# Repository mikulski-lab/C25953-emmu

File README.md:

# Atari XE C25953 emmu unit replicated in GAL16v8 and GAL20v10

As the happy owner of an Atari 65XE I wanted to upgrade it and have fun with full 130kB of RAM. After browsing the internet I learned that C25953 is very hard to find. There are some GAL implementations, however those require an extra D latch. Unfortunately my motherboard doesn't support such a solution.

After quick investigation, looking into C25953 discrete IC implementation's schematic, it turned out that it was possible to fully replicate C25953 logic with cheap, old, yet still available GALs (GAL16v8 and GAL20v10). The only trick was to generate the missing latched HALT signal used in logic equations.
Unfortunately due to the GALs' hardware restrictions __1:1 pin compatible__ replica __was not feasible__ forcing external wirings.

## Structure of the repository
  - gal16v8 - best to use with a custom PCB:
    - winculp - implementation in CUPL, jedec files, etc. 
    - graphics - photos of the implementation
    - kicad - kicad schematics/pcb and gerber files

  - gal22v10 - can be directly mounted in the socket, however requires some basic wiring and soldering on top of the IC:
    - winculp - implementation in CUPL, jedec files, etc.
    - graphics - photos of the implementation and wiring diagrams  

## Test result with "Video Blitz" demo

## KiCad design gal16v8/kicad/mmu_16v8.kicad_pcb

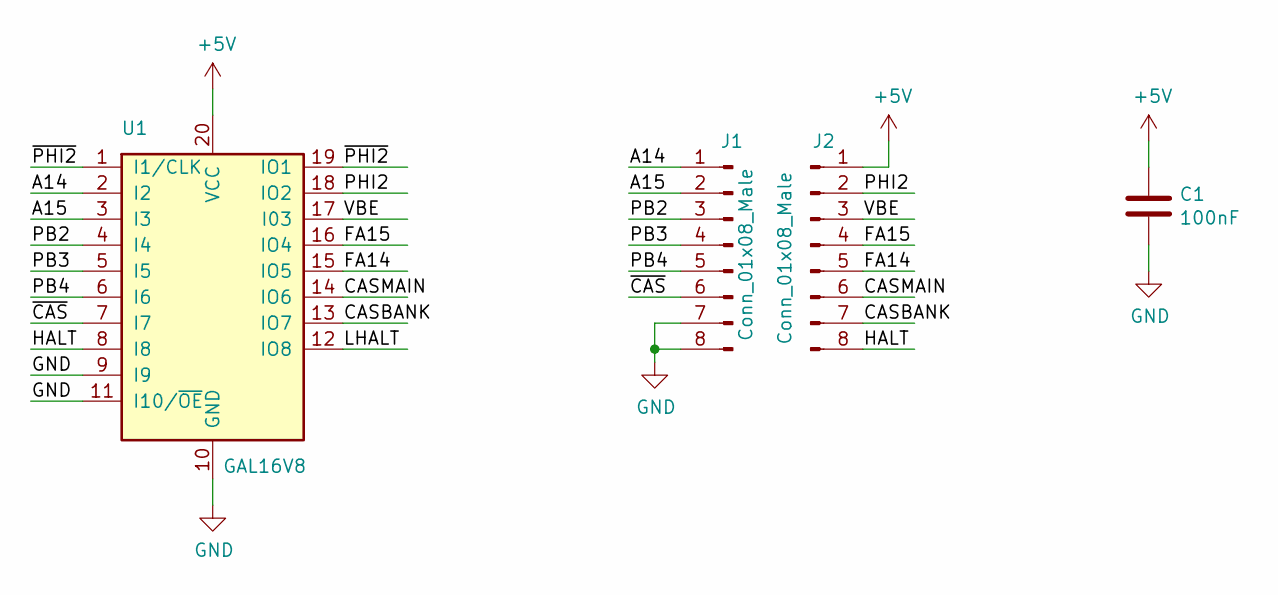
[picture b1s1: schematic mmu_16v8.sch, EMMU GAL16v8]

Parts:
C1: 100nF; C_0805_2012Metric_Pad1.15x1.40mm_HandSolder
J1, J2: Conn_01x08_Male; PinHeader_1x08_P2.54mm_Vertical
U1: GAL16V8; DIP-20_W7.62mm

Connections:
+5V: C1.1, J2.1, U1.20 (VCC)
/A14: J1.1, U1.2 (I2)
/A15: J1.2, U1.3 (I3)
/CASBANK: J2.7, U1.13 (IO7)
/CASMAIN: J2.6, U1.14 (IO6)
/FA14: J2.5, U1.15 (IO5)
/FA15: J2.4, U1.16 (IO4)
/HALT: J2.8, U1.8 (I8)
/LHALT: U1.12 (IO8)
/PB2: J1.3, U1.4 (I4)
/PB3: J1.4, U1.5 (I5)
/PB4: J1.5, U1.6 (I6)
/PHI2: J2.2, U1.18 (IO2)
/VBE: J2.3, U1.17 (I03)
/~CAS: J1.6, U1.7 (I7)
/~PHI2: U1.1 (I1/CLK), U1.19 (IO1)
GND: C1.2, J1.7, J1.8, U1.9 (I9), U1.10 (GND), U1.11 (I10/~OE~)

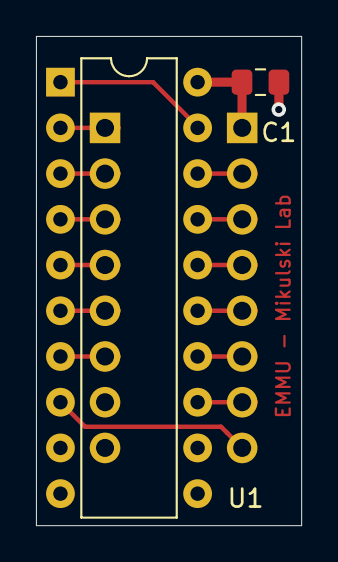
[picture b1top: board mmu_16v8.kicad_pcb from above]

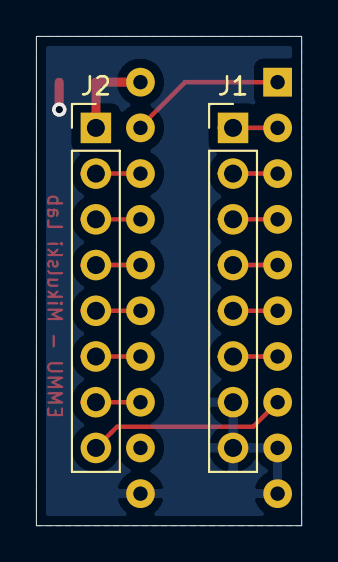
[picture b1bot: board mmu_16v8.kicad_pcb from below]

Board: 2 copper layers, 14.7 x 27.2 mm, 4 parts (2 on the bottom side), 16 nets.

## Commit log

2020-09-19 Update README.md
    Updated project description describing the project goals and the directory structure
2020-09-19 Update README.md
    Cosmetics changes to improve readability
2020-09-19 Updated content, wording fixes
2020-09-19 Switch to GPL prior initial commit of the source code
2020-09-19 Initial commit of the source files, etc.
2020-09-20 Downsizing the images
2020-09-23 22v10 photo without the tape
2020-09-24 Schematic and pcb exported to PNG
